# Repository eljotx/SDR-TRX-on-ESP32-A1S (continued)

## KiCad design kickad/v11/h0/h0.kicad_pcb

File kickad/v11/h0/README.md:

Practical tip for mounting anti noise capacitor C31.
The LM386 amplifier may sometimes oscillate at frequencies ranging from several tens of kilohertz to nearly 200 kHz (this is visible on the output when an oscilloscope is connected and is indicated by an operating current exceeding 100 mA). To prevent this, capacitor C31 should be soldered close to the LM386 chip; a good solution is to solder C31 directly onto resistor R10.

The system can be operated in a basic configuration without the AGC system and redundant components. The drawing shows which components do not need to be installed in such a case.

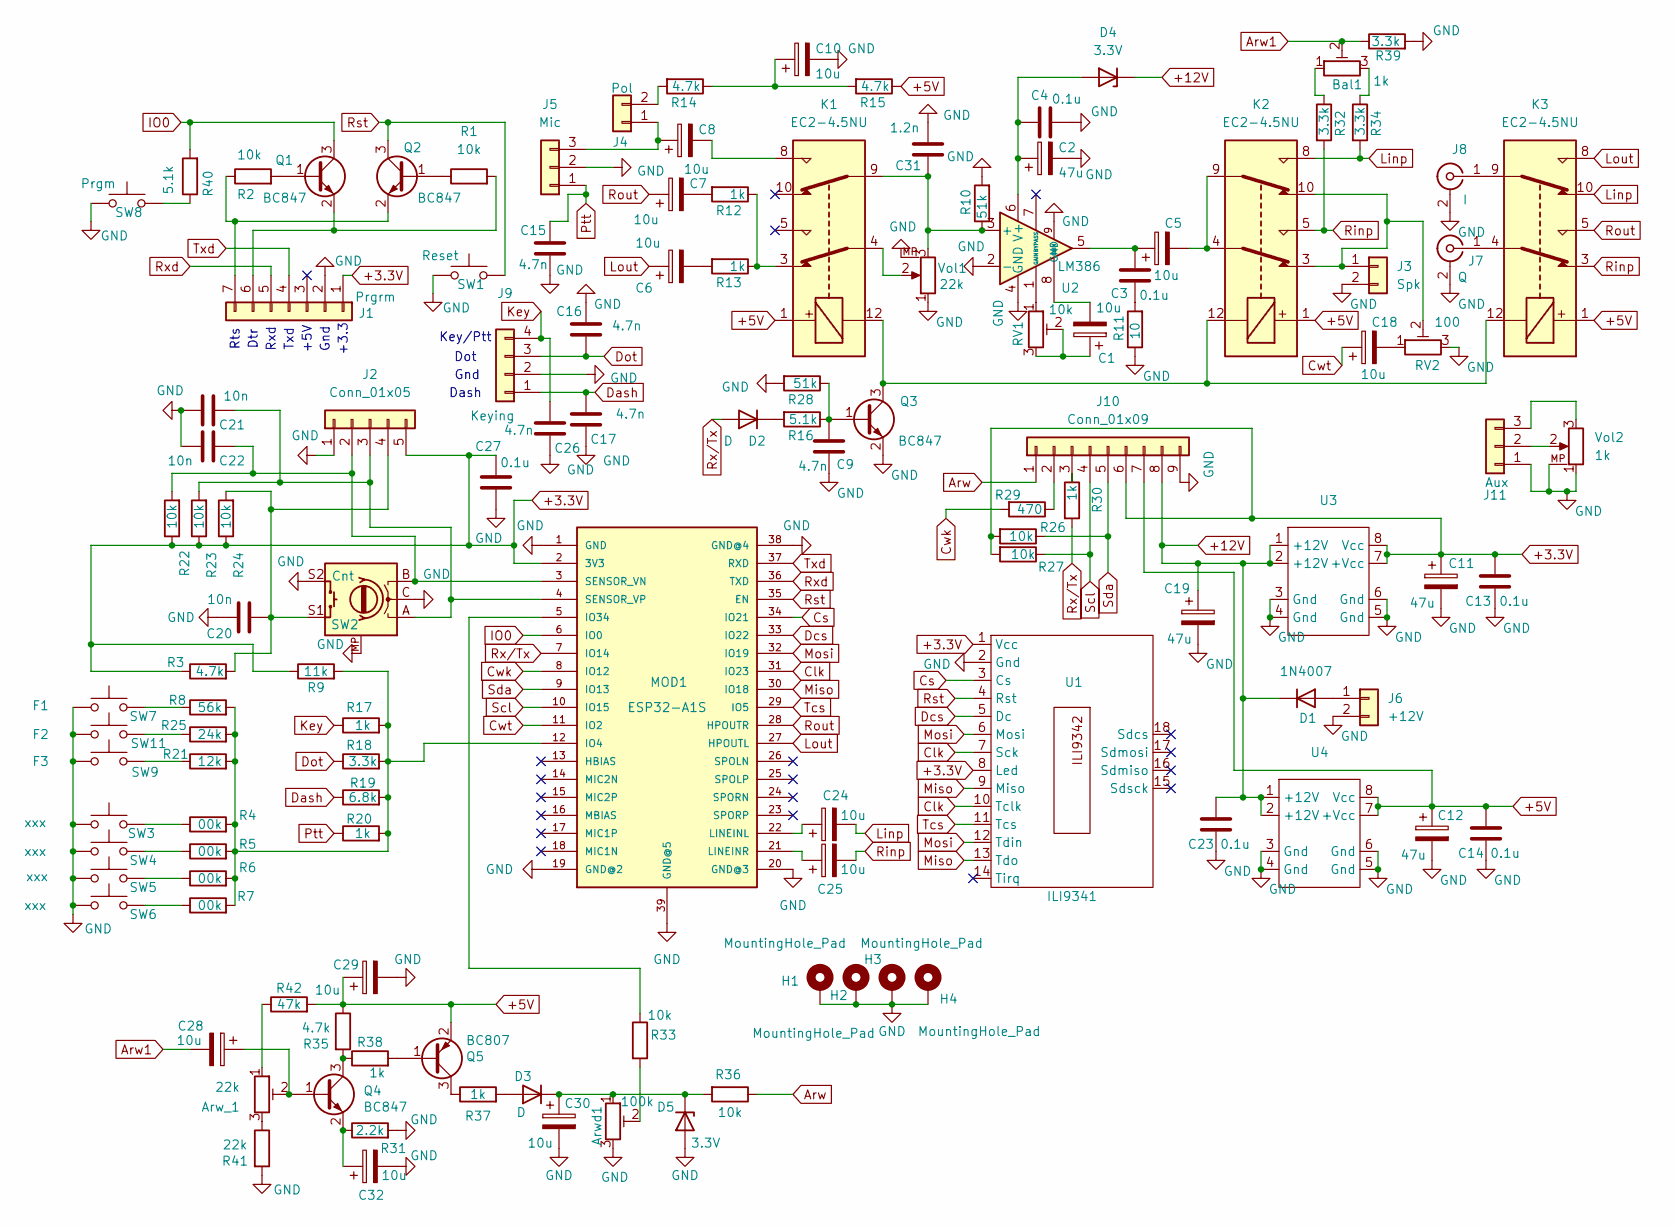
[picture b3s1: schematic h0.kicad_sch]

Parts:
Arw_1: 22k; Potentiometer_ACP_CA6-H2,5_Horizontal
Arwd1: 100k; Potentiometer_ACP_CA6-H2,5_Horizontal
Bal1: 1k; Potentiometer_ACP_CA6-H2,5_Horizontal
C1, C5, C6, C7, C8, C10, C18, C24, C25, C28, C29, C32: 10u; C_1206_3216Metric
C2, C11, C12, C19: 47u; CP_EIA-7343-31_Kemet-D
C3, C4, C13, C14, C23, C27: 0.1u; C_0805_2012Metric
C9, C15, C16, C17, C26: 4.7n; C_0805_2012Metric
C20, C21, C22: 10n; C_0805_2012Metric
C30: 10u; CP_EIA-7343-31_Kemet-D
C31: 1.2n; C_0805_2012Metric
D1: 1N4007; D_2114_3652Metric
D2, D3: D; C_1206_3216Metric
D4: 3.3V; D_DO-34_SOD68_P10.16mm_Horizontal
D5: 3.3V; C_1206_3216Metric
H1, H2, H3, H4: MountingHole_Pad; MountingHole_3.2mm_M3_Pad_Via
J1: Prgrm; PinHeader_1x07_P2.54mm_Vertical
J2: Conn_01x05; PinHeader_1x05_P2.54mm_Vertical
J3: Spk; power_con
J4: Pol; PinHeader_1x02_P2.54mm_Vertical
J5: Mic; PinHeader_1x03_P2.54mm_Vertical
J6: +12V; power_con
J7: Q; SMA_Amphenol_901-144_Vertical
J8: I; SMA_Amphenol_901-144_Vertical
J9: Keying; PinHeader_1x04_P2.54mm_Vertical
J10: Conn_01x09; PinHeader_1x09_P2.54mm_Vertical
J11: Aux; PinHeader_1x03_P2.54mm_Vertical
K1, K2, K3: EC2-4.5NU; Relay_DPDT_Kemet_EC2_NJ
MOD1: ESP32-A1S
Q1, Q2, Q3, Q4: BC847; SOT-23
Q5: BC807; SOT-23
R1, R2, R22, R23, R24, R26, R27, R33, R36: 10k; R_0805_2012Metric
R3, R14, R15, R35: 4.7k; R_0805_2012Metric
R4, R5, R6, R7: 00k; R_0805_2012Metric
R8: 56k; R_0805_2012Metric
R9: 11k; R_0805_2012Metric
R10, R28: 51k; R_0805_2012Metric
R11: 10; R_0805_2012Metric
R12, R13, R17, R20, R30, R37, R38: 1k; R_0805_2012Metric
R16, R40: 5.1k; R_0805_2012Metric
R18, R32, R34, R39: 3.3k; R_0805_2012Metric
R19: 6.8k; R_0805_2012Metric
R21: 12k; R_0805_2012Metric
R25: 24k; R_0805_2012Metric
R29: 470; R_0805_2012Metric
R31: 2.2k; R_0805_2012Metric
R41: 22k; R_0805_2012Metric
R42: 47k; R_0805_2012Metric
RV1: 10k; Potentiometer_ACP_CA6-H2,5_Horizontal
RV2: 100; Potentiometer_ACP_CA6-H2,5_Horizontal
SW1: Reset; microswitch
SW2: Cnt; RotaryEncoder_Alps_EC11E-Switch_Vertical_H20mm
SW3, SW4, SW5, SW6: xxx; microswitch
SW7: F1; microswitch
SW8: Prgm; microswitch
SW9: F3; microswitch
SW11: F2; microswitch
U1: ILI9341; ili9342
U2: LM386; Diodes_PSOP-8
U3, U4: dc-dc
Vol1: 22k; Potentiometer_Alpha_RD901F-40-00D_Single_Vertical
Vol2: 1k; Potentiometer_Alpha_RD901F-40-00D_Single_Vertical

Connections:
+3.3V: C11.1, C13.1, C27.1, J1.1, J2.5, J10.6, MOD1.2 (3V3), R3.1, R9.1, R22.1, R23.1, R24.1, R26.2, R27.2, U1.1 (Vcc), U1.8 (Led), U3.7 (+Vcc), U3.8 (Vcc)
+5V: C12.1, C14.1, C29.1, J10.7, K1.1, K2.1, K3.1, Q5.2 (E), R15.1, R35.1, R42.2, U4.7 (+Vcc), U4.8 (Vcc)
+12V: C19.1, C23.1, D1.1 (K), D4.1 (K), J10.8, U3.1 (+12V), U3.2 (+12V), U4.1 (+12V), U4.2 (+12V)
Arw: J10.1, R36.1
Arw1: Bal1.2, C28.2, R39.1
Clk: MOD1.31 (IO23), U1.7 (Sck), U1.10 (Tclk)
Cs: MOD1.34 (IO21), U1.3 (Cs)
Cwk: MOD1.8 (IO12), R29.2
Cwt: C18.1, MOD1.11 (IO2)
Dash: C17.1, J9.1, R19.1
Dcs: MOD1.33 (IO22), U1.5 (Dc)
Dot: C16.2, J9.3, R18.1
GND: Arwd1.3, C2.2, C4.2, C9.1, C10.2, C11.2, C12.2, C13.2, C14.2, C15.2, C16.1, C17.2, C19.2, C20.1, C21.1, C22.1, C23.2, C26.2, C27.2, C29.2, C30.2, C31.2, C32.2, D5.2 (A), H1.1, H2.1, H3.1, H4.1, J1.2, J2.1, J3.2, J5.2, J6.2, J7.2 (Ext), J8.2 (Ext), J9.2, J10.9, J11.1, MOD1.1 (GND), MOD1.19 (GND@2), MOD1.20 (GND@3), MOD1.38 (GND@4), MOD1.39 (GND@5), Q3.2 (E), R10.2, R11.1, R28.2, R31.2, R39.2, R41.2, RV2.3, SW1.1, SW2.C, SW2.MP, SW2.S2, SW3.1, SW4.1, SW5.1, SW6.1, SW7.1, SW8.1, SW9.1, SW11.1, U1.2 (Gnd), U2.2 (-), U2.4 (GND), U2.9 (GND), U3.3 (Gnd), U3.4 (Gnd), U3.5 (Gnd), U3.6 (Gnd), U4.3 (Gnd), U4.4 (Gnd), U4.5 (Gnd), U4.6 (Gnd), Vol1.1, Vol1.MP, Vol2.1, Vol2.MP
IO0: MOD1.6 (IO0), Q1.3 (C), R40.2
Key: C26.1, J9.4, R17.1
Linp: C24.2, K2.8, K3.10, R34.2
Lout: C6.1, K3.8, MOD1.27 (HPOUTL)
Miso: MOD1.30 (IO18), U1.9 (Miso), U1.13 (Tdo)
Mosi: MOD1.32 (IO19), U1.6 (Mosi), U1.12 (Tdin)
unnamed: Arw_1.1, R42.1
unnamed: Arw_1.3, R41.1
unnamed: Arwd1.2, R33.2
unnamed: Bal1.1, R32.1
unnamed: Bal1.3, R34.1
unnamed: C1.1, RV1.2, RV1.3
unnamed: C1.2, U2.8 (GAIN)
unnamed: C3.1, C5.1, U2.5
unnamed: C3.2, R11.2
unnamed: C5.2, K2.4, K2.9
unnamed: C6.2, R13.2
unnamed: C7.2, R12.2
unnamed: C8.2, K1.8
unnamed: C10.1, R14.1, R15.2
unnamed: C18.2, RV2.1
unnamed: D1.2 (A), J6.1
unnamed: D2.1 (K), R16.2
unnamed: D3.2 (A), R37.2
unnamed: Arwd1.1, C30.1, D3.1 (K), D5.1 (K), R36.2
unnamed: C2.1, C4.1, D4.2 (A), U2.6 (V+)
unnamed: J1.6, Q1.2 (E), R1.2
unnamed: J1.7, Q2.2 (E), R2.1
unnamed: C22.2, J2.2, MOD1.3 (SENSOR_VN), R22.2, SW2.B
unnamed: C21.2, J2.3, MOD1.4 (SENSOR_VP), R23.2, SW2.A
unnamed: C20.2, J2.4, R3.2, R24.2, SW2.S1
unnamed: J3.1, K2.3, K2.10, RV2.2
unnamed: C8.1, J4.1, J5.3
unnamed: J4.2, R14.2
unnamed: J7.1 (In), K3.4
unnamed: J8.1 (In), K3.9
unnamed: J10.2, R29.1
unnamed: J10.3, R30.1
unnamed: J11.2, Vol2.2
unnamed: J11.3, Vol2.3
unnamed: K1.3, R12.1, R13.1
unnamed: K1.4, Vol1.2
unnamed: MOD1.12 (IO4), R4.2, R5.2, R6.2, R7.2, R8.2, R9.2, R17.2, R18.2, R19.2, R20.2, R21.2, R25.2
unnamed: MOD1.5 (IO34), R33.1
unnamed: C24.1, MOD1.22 (LINEINL)
unnamed: C25.1, MOD1.21 (LINEINR)
unnamed: Q1.1 (B), R2.2
unnamed: Q2.1 (B), R1.1
unnamed: C9.2, Q3.1 (B), R16.1, R28.1
unnamed: K1.12, K2.12, K3.12, Q3.3 (C)
unnamed: Arw_1.2, C28.1, Q4.1 (B)
unnamed: Q4.3 (C), R35.2, R38.1
unnamed: C32.1, Q4.2 (E), R31.1
unnamed: Q5.1 (B), R38.2
unnamed: Q5.3 (C), R37.1
unnamed: R4.1, SW3.2
unnamed: R5.1, SW4.2
unnamed: R6.1, SW5.2
unnamed: R7.1, SW6.2
unnamed: R8.1, SW7.2
unnamed: R21.1, SW9.2
unnamed: R25.1, SW11.2
unnamed: R40.1, SW8.2
unnamed: RV1.1, U2.1 (GAIN)
unnamed: C31.1, K1.9, R10.1, U2.3 (+), Vol1.3
Ptt: C15.1, J5.1, R20.1
Rinp: C25.2, K2.5, K3.3, R32.2
Rout: C7.1, K3.5, MOD1.28 (HPOUTR)
Rst: MOD1.35 (EN), Q2.3 (C), SW1.2, U1.4 (Rst)
Rxd: J1.5, MOD1.36 (TXD)
Rx/Tx: D2.2 (A), MOD1.7 (IO14), R30.2
Scl: J10.4, MOD1.10 (IO15), R27.1
Sda: J10.5, MOD1.9 (IO13), R26.1
Tcs: MOD1.29 (IO5), U1.11 (Tcs)
Txd: J1.4, MOD1.37 (RXD)

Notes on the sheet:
Dtr
Key/Ptt
+5V
+3.3
Txd
Gnd
Dot
Rts
Dash
Rxd

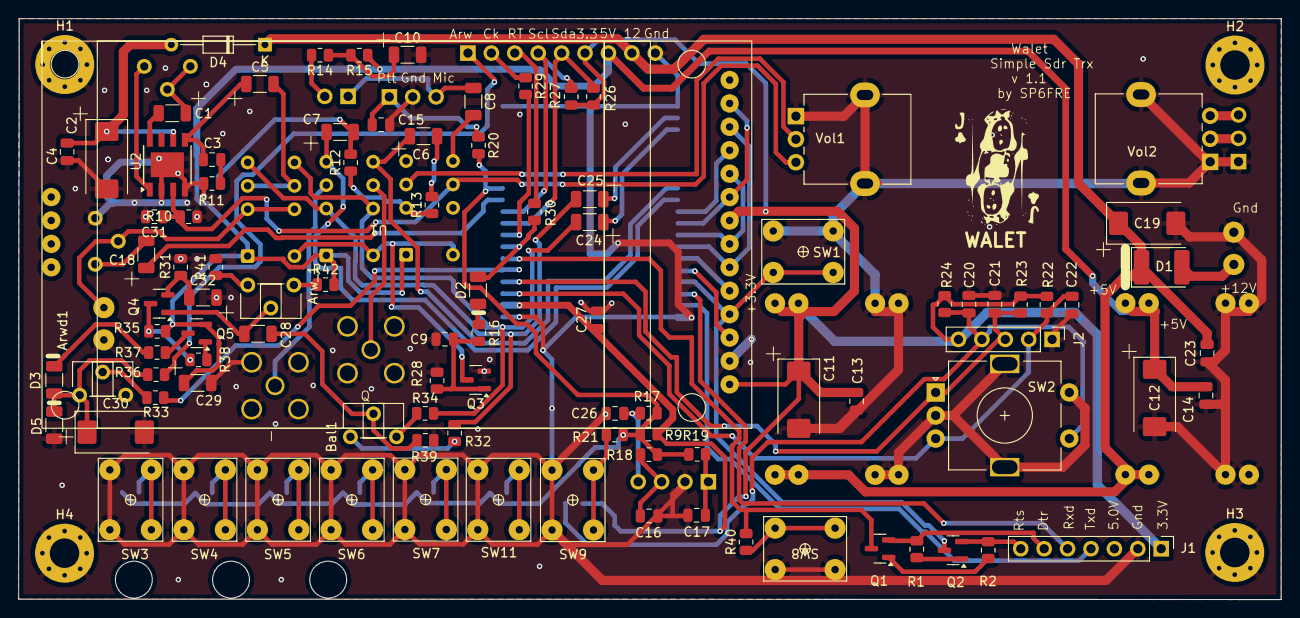
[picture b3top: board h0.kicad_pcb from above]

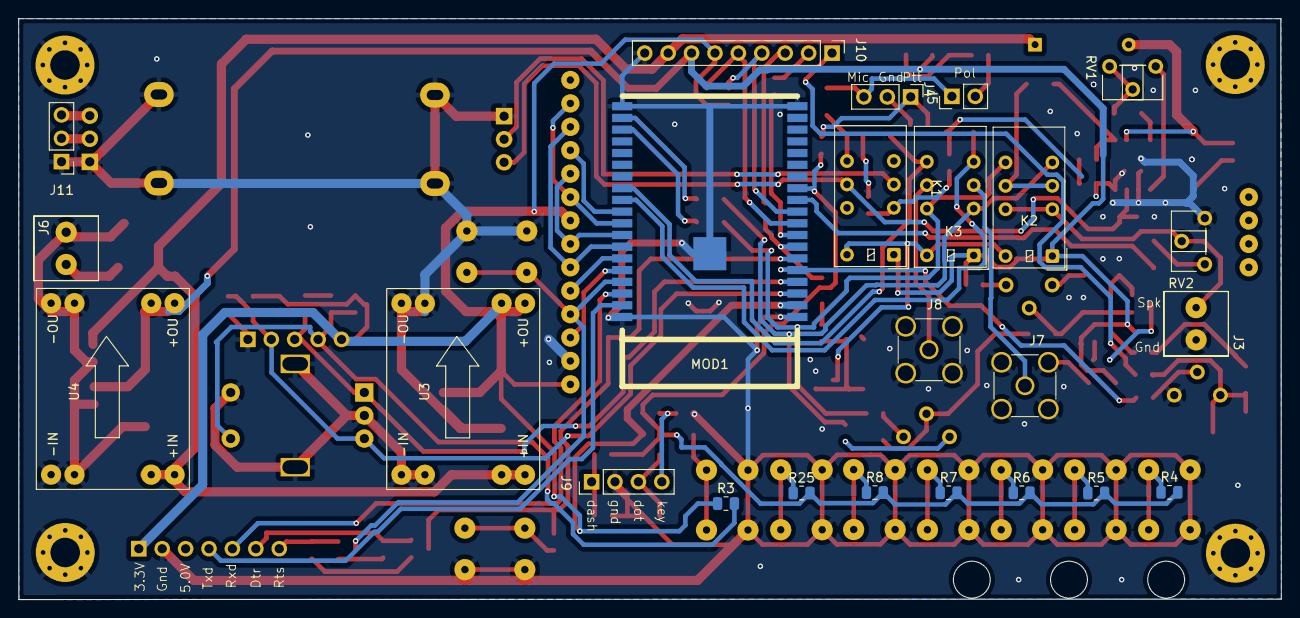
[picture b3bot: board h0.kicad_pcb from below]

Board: 2 copper layers, 137.0 x 63.0 mm, 125 parts (24 on the bottom side), 88 nets.

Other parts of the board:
WALET: LOGO; walet0

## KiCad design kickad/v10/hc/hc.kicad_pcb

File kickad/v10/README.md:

Kickad files was created with KicCad version 8.09-1

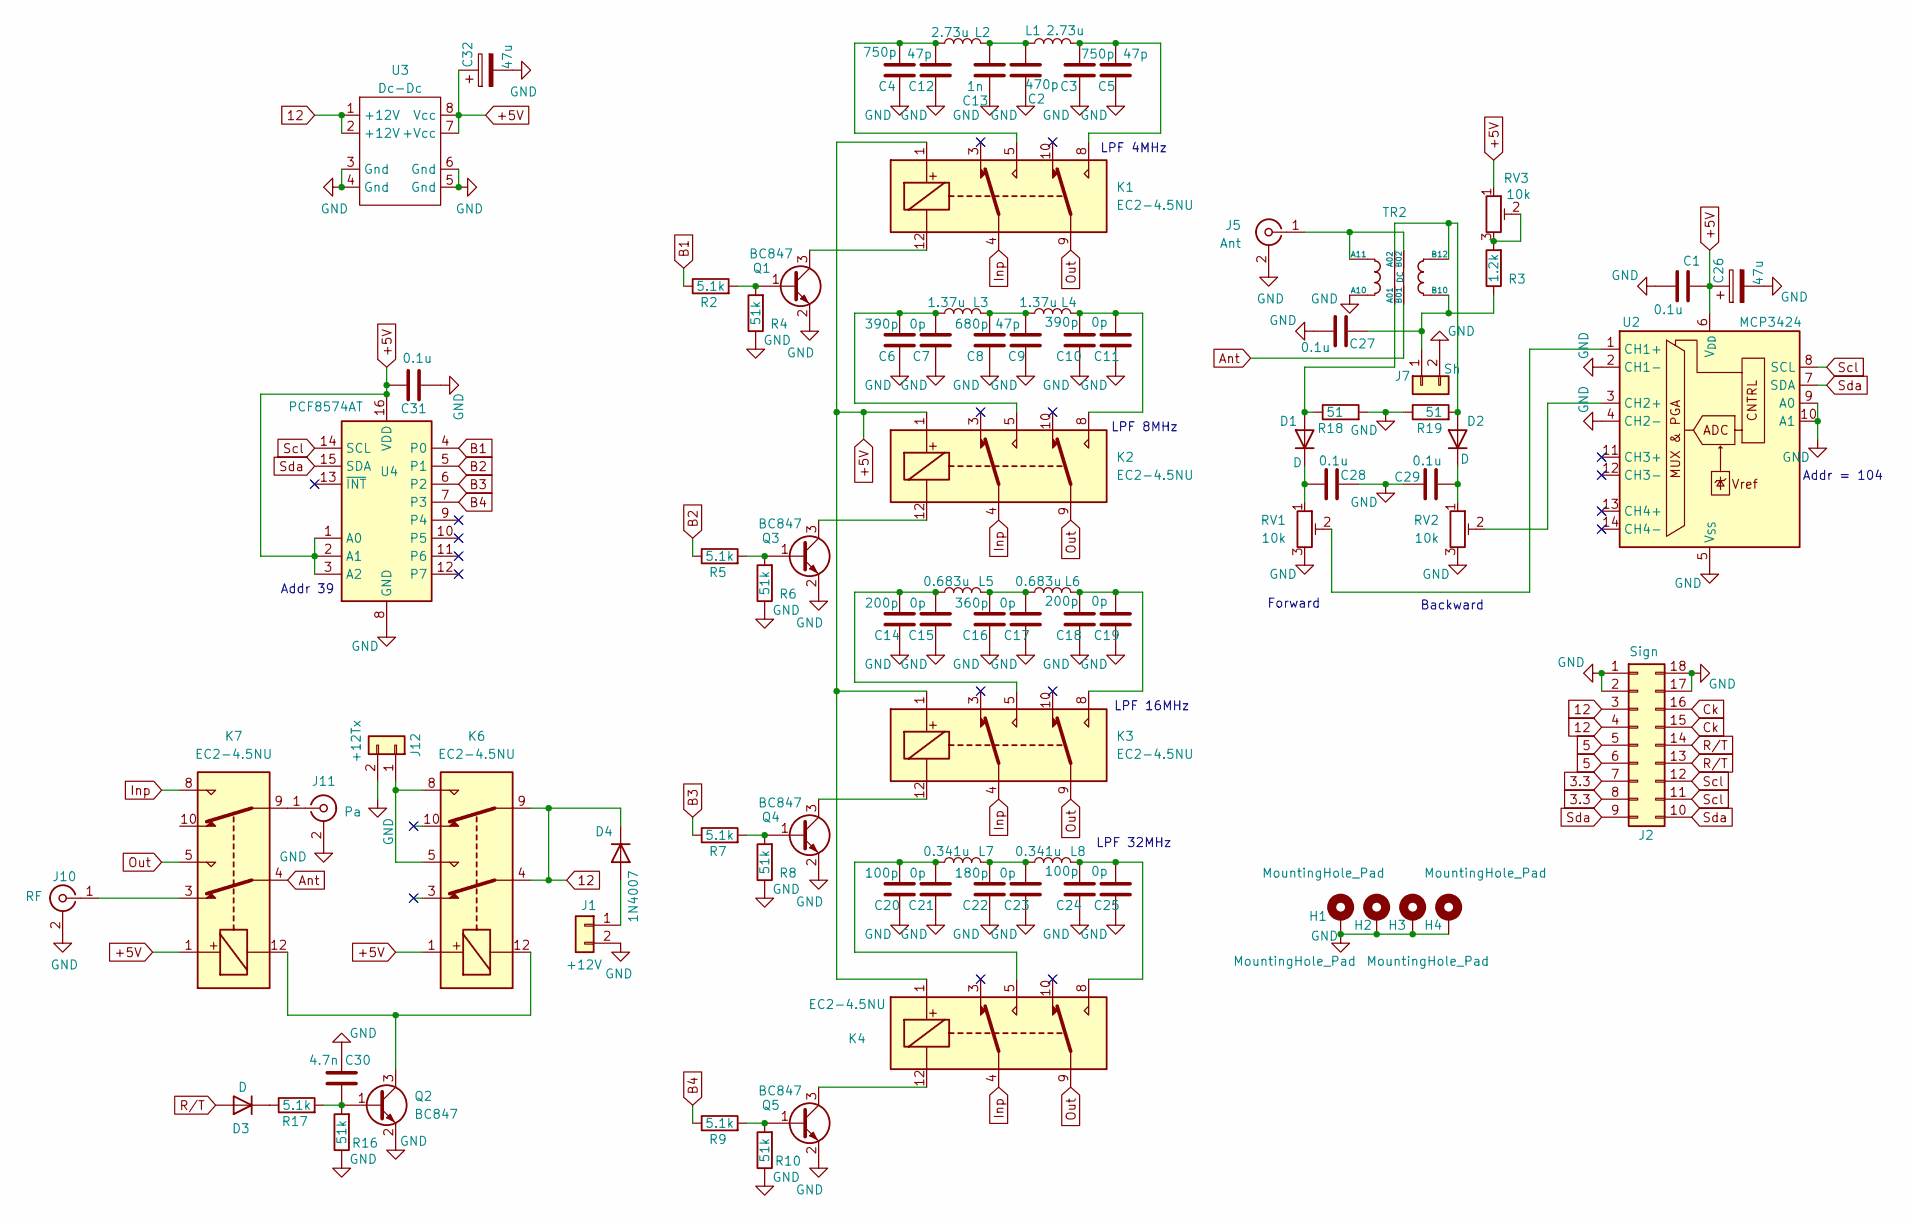
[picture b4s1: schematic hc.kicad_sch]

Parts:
C1, C27, C28, C29, C31: 0.1u; C_0805_2012Metric
C2: 470p; C_1206_3216Metric
C3, C4: 750p; C_1206_3216Metric
C5, C9, C12: 47p; C_1206_3216Metric
C6, C10: 390p; C_1206_3216Metric
C7, C11, C15, C17, C19, C21, C23, C25: 0p; C_1206_3216Metric
C8: 680p; C_1206_3216Metric
C13: 1n; C_1206_3216Metric
C14, C18: 200p; C_1206_3216Metric
C16: 360p; C_1206_3216Metric
C20, C24: 100p; C_1206_3216Metric
C22: 180p; C_1206_3216Metric
C26, C32: 47u; CP_EIA-3528-21_Kemet-B
C30: 4.7n; C_0805_2012Metric
D1, D2, D3: D; D_1206_3216Metric
D4: 1N4007; D_1206_3216Metric
H1, H2, H3, H4: MountingHole_Pad; MountingHole_3.2mm_M3_Pad_Via
J1: +12V; power_con
J2: Sign; PinHeader_2x09_P2.54mm_Vertical
J5: Ant; SMA_Amphenol_901-144_Vertical
J7: Sh; PinHeader_1x02_P2.54mm_Vertical
J10: RF; SMA_Amphenol_901-144_Vertical
J11: Pa; SMA_Amphenol_901-144_Vertical
J12: +12Tx; power_con
K1, K2, K3, K4, K6, K7: EC2-4.5NU; Relay_DPDT_Kemet_EC2_NU
L1, L2: 2.73u; l_01
L3, L4: 1.37u; l_01
L5, L6: 0.683u; l_01
L7, L8: 0.341u; l_01
Q1, Q2, Q3, Q4, Q5: BC847; SOT-23
R2, R5, R7, R9, R17: 5.1k; R_0805_2012Metric
R3: 1.2k; R_0805_2012Metric
R4, R6, R8, R10, R16: 51k; R_0805_2012Metric
R18, R19: 51; R_Axial_DIN0309_L9.0mm_D3.2mm_P12.70mm_Horizontal
RV1, RV2, RV3: 10k; Potentiometer_ACP_CA6-H2,5_Horizontal
TR2: DC; dircoupler
U2: MCP3424; SOIC-14_3.9x8.7mm_P1.27mm
U3: Dc-Dc; dc-dc
U4: PCF8574AT; SOIC-16W_7.5x10.3mm_P1.27mm

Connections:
3.3: J2.7, J2.8
5: J2.5, J2.6
12: D4.1 (K), J2.3, J2.4, K6.4, K6.9, U3.1 (+12V), U3.2 (+12V)
+5V: C1.2, C26.1, C31.1, C32.1, K1.1, K2.1, K3.1, K4.1, K6.1, K7.1, RV3.1, U2.6 (V_{DD}), U3.7 (+Vcc), U3.8 (Vcc), U4.1 (A0), U4.2 (A1), U4.3 (A2), U4.16 (VDD)
Ant: K7.4, TR2.3 (B01)
B1: R2.1, U4.4 (P0)
B2: R5.1, U4.5 (P1)
B3: R7.1, U4.6 (P2)
B4: R9.1, U4.7 (P3)
Ck: J2.15, J2.16
GND: C1.1, C2.1, C3.1, C4.1, C5.1, C6.1, C7.1, C8.1, C9.1, C10.1, C11.1, C12.1, C13.1, C14.1, C15.1, C16.1, C17.1, C18.1, C19.1, C20.1, C21.1, C22.1, C23.1, C24.1, C25.1, C26.2, C27.1, C28.1, C29.2, C30.1, C31.2, C32.2, H1.1, H2.1, H3.1, H4.1, J1.2, J2.1, J2.2, J2.17, J2.18, J5.2 (Ext), J7.2, J10.2 (Ext), J11.2 (Ext), J12.2, Q1.2 (E), Q2.2 (E), Q3.2 (E), Q4.2 (E), Q5.2 (E), R4.1, R6.1, R8.1, R10.1, R16.1, R18.2, R19.1, RV1.3, RV2.3, TR2.5 (A10), U2.2 (CH1-), U2.4 (CH2-), U2.5 (V_{SS}), U2.9 (A0), U2.10 (A1), U3.3 (Gnd), U3.4 (Gnd), U3.5 (Gnd), U3.6 (Gnd), U4.8 (GND)
Inp: K1.4, K2.4, K3.4, K4.4, K7.8
unnamed: C3.2, C5.2, K1.8, L1.2
unnamed: C6.2, C7.2, K2.5, L3.1
unnamed: C8.2, C9.2, L3.2, L4.1
unnamed: C10.2, C11.2, K2.8, L4.2
unnamed: C4.2, C12.2, K1.5, L2.1
unnamed: C2.2, C13.2, L1.1, L2.2
unnamed: C14.2, C15.2, K3.5, L5.1
unnamed: C16.2, C17.2, L5.2, L6.1
unnamed: C18.2, C19.2, K3.8, L6.2
unnamed: C20.2, C21.2, K4.5, L7.1
unnamed: C22.2, C23.2, L7.2, L8.1
unnamed: C24.2, C25.2, K4.8, L8.2
unnamed: D1.2 (A), R18.1, TR2.1 (A01)
unnamed: C28.2, D1.1 (K), RV1.1
unnamed: D2.2 (A), R19.2, TR2.2 (A02), TR2.8 (B12)
unnamed: C29.1, D2.1 (K), RV2.1
unnamed: D3.1 (K), R17.1
unnamed: D4.2 (A), J1.1
unnamed: J5.1 (In), TR2.4 (B02), TR2.6 (A11)
unnamed: C27.2, J7.1, R3.1, TR2.7 (B10)
unnamed: J10.1 (In), K7.3
unnamed: J11.1 (In), K7.9
unnamed: J12.1, K6.5, K6.8
unnamed: Q1.1 (B), R2.2, R4.2
unnamed: K1.12, Q1.3 (C)
unnamed: C30.2, Q2.1 (B), R16.2, R17.2
unnamed: K6.12, K7.12, Q2.3 (C)
unnamed: Q3.1 (B), R5.2, R6.2
unnamed: K2.12, Q3.3 (C)
unnamed: Q4.1 (B), R7.2, R8.2
unnamed: K3.12, Q4.3 (C)
unnamed: Q5.1 (B), R9.2, R10.2
unnamed: K4.12, Q5.3 (C)
unnamed: R3.2, RV3.2, RV3.3
unnamed: RV1.2, U2.1 (CH1+)
unnamed: RV2.2, U2.3 (CH2+)
Out: K1.9, K2.9, K3.9, K4.9, K7.5
R/T: D3.2 (A), J2.13, J2.14
Scl: J2.11, J2.12, U2.8 (SCL), U4.14 (SCL)
Sda: J2.9, J2.10, U2.7 (SDA), U4.15 (SDA)

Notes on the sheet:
LPF 8MHz
Addr = 104
Addr 39
LPF 16MHz
LPF 32MHz
Backward
LPF 4MHz
Forward

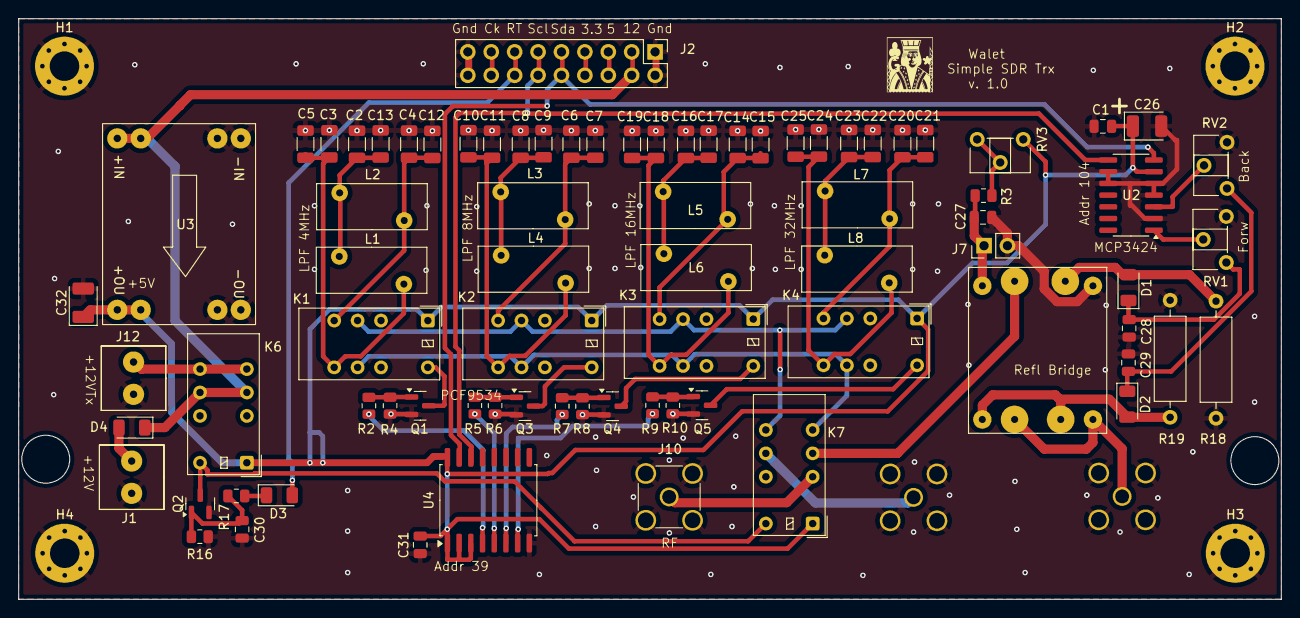
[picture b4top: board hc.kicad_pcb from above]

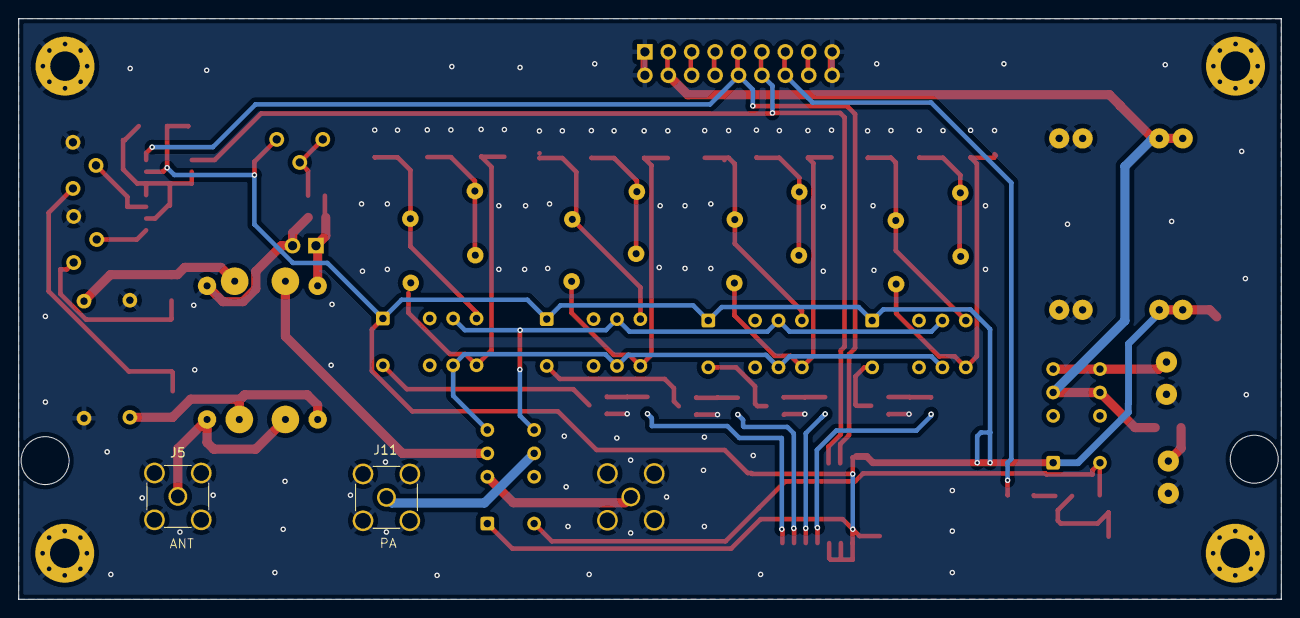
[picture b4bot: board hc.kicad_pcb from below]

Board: 2 copper layers, 137.0 x 63.0 mm, 86 parts (2 on the bottom side), 52 nets.

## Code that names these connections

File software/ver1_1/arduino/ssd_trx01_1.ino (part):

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#define LOGO_HEIGHT 120
#define LOGO_WIDTH 240
#define RxTx_port 14  //port Rx/TX
#define Cwk_port 12   //port CW keying
#define Cwt_port 2    //CW ton 800Hz
#define Arw 34
#define But2s 4
#define RxTx_led_x 232
#define RxTx_led_y 13
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  xTaskCreatePinnedToCore(Task0code, "Task0", 25000, NULL, 1, &Task0, 0);

  pinMode(RxTx_port, OUTPUT);
  pinMode(Cwk_port, OUTPUT);
  pinMode(Cwt_port, OUTPUT);
  digitalWrite(Cwt_port, LOW);
  analogWriteFrequency(Cwt_port, 800);  //setting cw ton frequency
  analogWrite(Cwt_port, 0);             //ton generator off
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    } else if (button_value < 2160 && button_value >= 1605) {
      button_nr = 4;  //button F3
    } else if (button_value < 1605 && button_value >= 1035) {
      button_nr = 3;  //button dash
    } else if (button_value < 1035 && button_value >= 460) {
      button_nr = 2;  //button dot
    } else if (button_value < 460) {
      button_nr = 1;  //button key/ptt
    }
  } else {
    button_nr = 7;  // no button pressed
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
